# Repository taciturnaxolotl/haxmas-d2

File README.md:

# Haxmas pcb tree

This is a little pcb tree I made for hackclub's 2025 haxmas day 2. It should theoretically slot together and work fairly well as long as I did everything correctly lol.

<p align="center">
    <i><code>&copy 2025-present <a href="https://github.com/taciturnaxololt">Kieran Klukas</a></code></i>
</p>

<p align="center">
    
</p>

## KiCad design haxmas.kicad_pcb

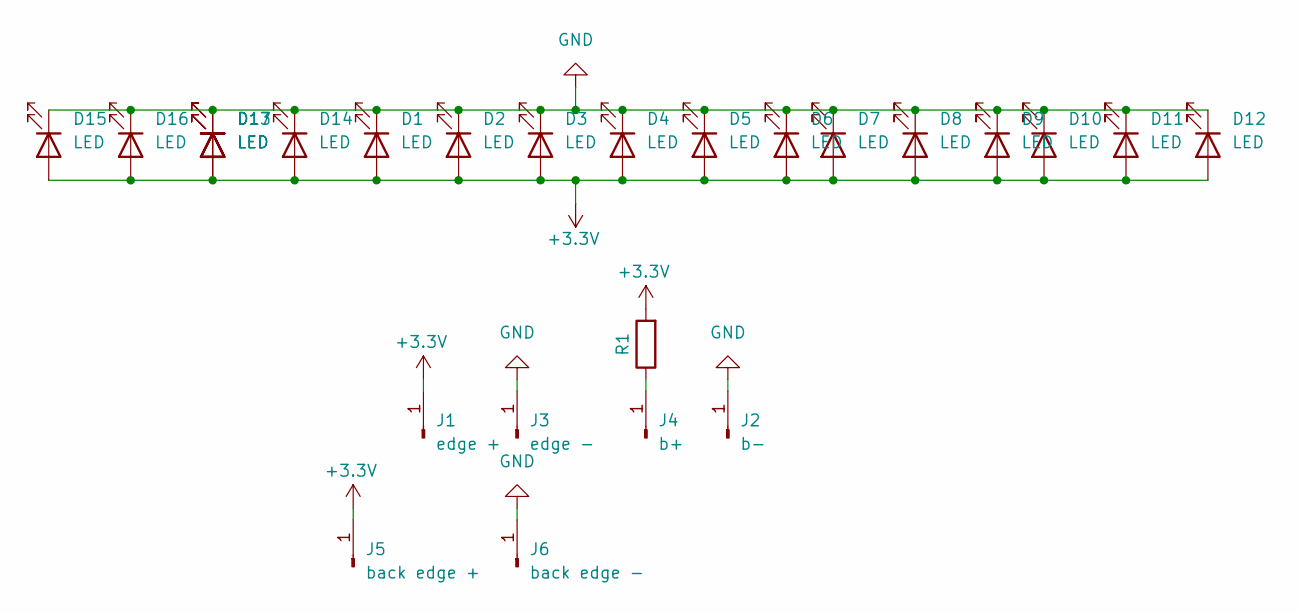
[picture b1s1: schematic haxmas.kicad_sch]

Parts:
D1, D2, D3, D4, D5, D6, D7, D8, D9, D10, D11, D12, D13, D14, D15, D16, D17: LED; LED_D3.0mm
J1: edge +; SolderWirePad_1x01_SMD_2x4mm
J2: b-; SolderWirePad_1x01_SMD_2x4mm
J3: edge -; SolderWirePad_1x01_SMD_2x4mm
J4: b+; SolderWirePad_1x01_SMD_2x4mm
J5: back edge +; SolderWirePad_1x01_SMD_2x4mm
J6: back edge -; SolderWirePad_1x01_SMD_2x4mm
R1: R; R_Axial_DIN0204_L3.6mm_D1.6mm_P7.62mm_Horizontal

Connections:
+3.3V: D1.2 (A), D2.2 (A), D3.2 (A), D4.2 (A), D5.2 (A), D6.2 (A), D7.2 (A), D8.2 (A), D9.2 (A), D10.2 (A), D11.2 (A), D12.2 (A), D13.2 (A), D14.2 (A), D15.2 (A), D16.2 (A), D17.2 (A), J1.1, J5.1, R1.2
GND: D1.1 (K), D2.1 (K), D3.1 (K), D4.1 (K), D5.1 (K), D6.1 (K), D7.1 (K), D8.1 (K), D9.1 (K), D10.1 (K), D11.1 (K), D12.1 (K), D13.1 (K), D14.1 (K), D15.1 (K), D16.1 (K), D17.1 (K), J2.1, J3.1, J6.1
unnamed: J4.1, R1.1

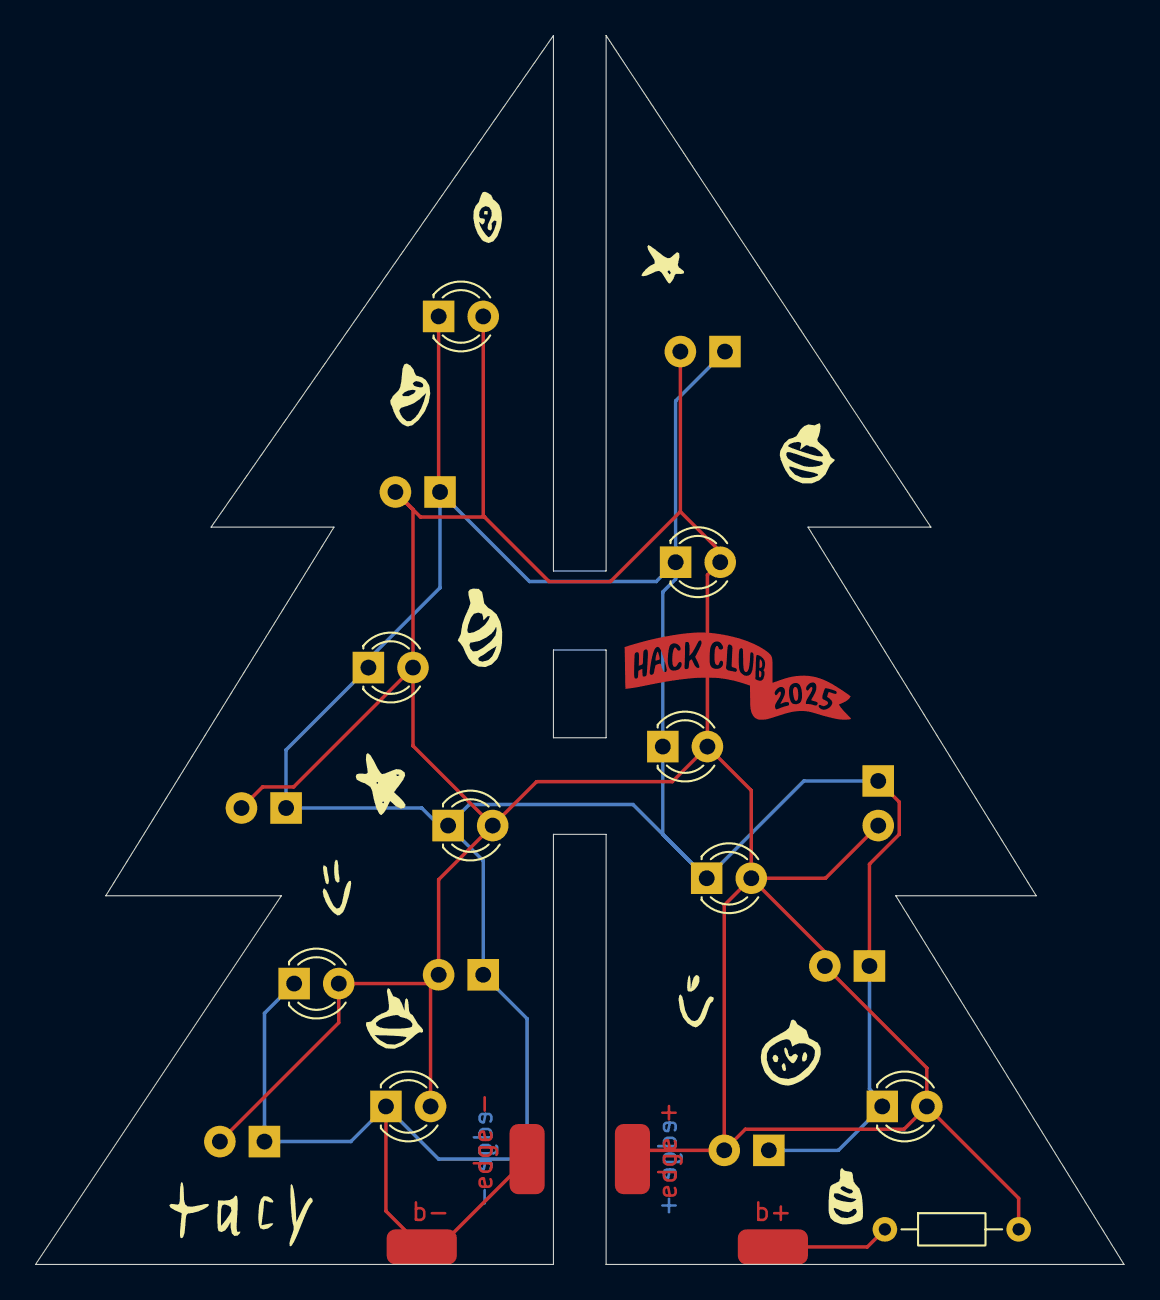
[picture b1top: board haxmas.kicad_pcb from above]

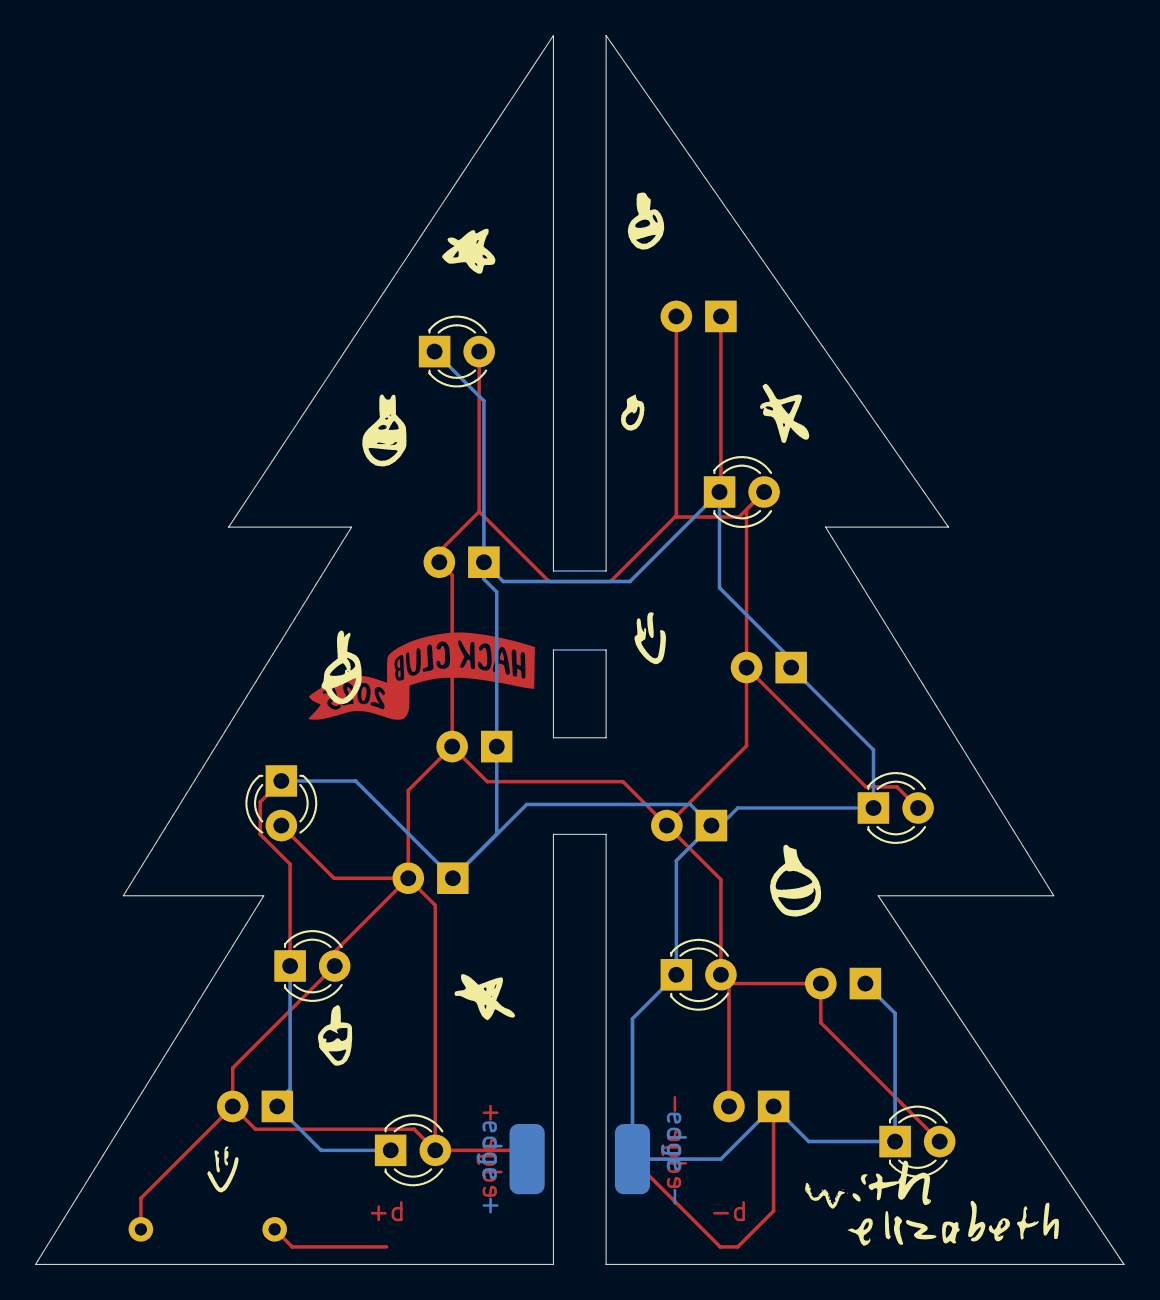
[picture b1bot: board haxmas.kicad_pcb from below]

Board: 2 copper layers, 62.0 x 70.0 mm, 29 parts (10 on the bottom side), 3 nets.

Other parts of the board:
KiKit_MB_4_1, KiKit_MB_4_2, KiKit_MB_4_3, KiKit_MB_4_4, KiKit_MB_4_5: NPTH

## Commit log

2025-12-15 feat: tiny version
2025-12-15 feat: add large version
2025-12-15 feat: add prod fil;es
2025-12-15 docs: add more info
